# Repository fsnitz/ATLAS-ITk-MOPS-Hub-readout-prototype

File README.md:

# MPSoC-based MOPS-Hub readout board — supplementary project files

This repository accompanies the master's thesis **“Development of an MPSoC-based readout board as a verification method and interface for the ATLAS ITk MOPS-Hub communication interface”** (2024).

The work addresses an intermediate readout system for the ATLAS Inner Tracker (ITk) Pixel Detector Control System. It uses the AMD Kria K26 System-on-Module (SoM) with programmable logic (PL) and a processing system (PS), PetaLinux, an AXI-based shared-memory interface, and an electrical link (eLink) to communicate with the MOPS-Hub. The **eLink** is the electrical communication link; the **eLink Core** is its FPGA firmware implementation.

> **Project status:** The PL–PS shared-memory interface was successfully tested. The eLink interface exhibited firmware-timing and hardware/signal-integrity limitations. Full readout-chain functionality was **not verified** within the thesis. The published files should therefore be treated as research and development artifacts, not as a validated production design.
>
> **Before publishing this repository:** Copy the actual project files into the paths listed below, preserving capitalization and filenames. These links are derived from the original thesis appendix and cannot be verified until the repository has been populated. Check that you have permission to redistribute third-party documentation, vendor files, externally developed tools, and CERN/project-specific materials. If a file cannot be released, remove its repository link and cite the authorized upstream source instead.

## Getting started

1. Consult the thesis for the system architecture, implementation decisions, test setup, results, and limitations.
2. For Vivado project generation, start with the [firmware build instructions](Firmware/BuildScripts/README.md) and the relevant build script below. The thesis used the **2023.2** versions of Vivado and PetaLinux; confirm any additional requirements in the build instructions.
3. For embedded Linux, see the [PetaLinux projects](Software/PetaLinuxProjects/) and associated tools under [ToolsAndLibs](Software/ToolsAndLibs/).
4. For the eLink adapter, see the [KR260 eLink-hat revisions](Hardware/KR260eLinkHat/). The second revision includes changes for receiver-side common-mode biasing.
5. Use a tagged release of this repository when reproducing the thesis, because its main development branch may change over time.

## Repository contents

This [README](README.md) is the index of the supplementary materials.

The five principal directories are [Hardware/](Hardware/), [Firmware/](Firmware/), [Software/](Software/), [Documentation/](Documentation/), and [Miscellaneous/](Miscellaneous/). Links below are **relative to the root of this repository**.

### Hardware

- [Hardware/KR260eLinkHat/](Hardware/KR260eLinkHat/) — adapter board for interfacing the KR260 evaluation board with the eLink signals.
  - [rev01/](Hardware/KR260eLinkHat/rev01/) — initial design, used during the thesis.
    - [KR260eLinkHatSchematics_Rev01.pdf](Hardware/KR260eLinkHat/rev01/KR260eLinkHatSchematics_Rev01.pdf) — revision 01 schematic (thesis Appendix A.1).
    - [eLinkHatPCB_Rev01.pdf](Hardware/KR260eLinkHat/rev01/eLinkHatPCB_Rev01.pdf) — revision 01 PCB layout (Appendix A.2).
  - [rev02/](Hardware/KR260eLinkHat/rev02/) — revision incorporating biasing changes for LVDS receiver common-mode voltage.
    - [KR260eLinkHatSchematics_Rev02.pdf](Hardware/KR260eLinkHat/rev02/KR260eLinkHatSchematics_Rev02.pdf) — revision 02 schematic (Appendix A.3).
    - [eLinkHatPCB_Rev02.pdf](Hardware/KR260eLinkHat/rev02/eLinkHatPCB_Rev02.pdf) — revision 02 PCB layout (Appendix A.4).
- [Hardware/Library/](Hardware/Library/) — KiCad symbols, footprints, and 3D models supplementing the standard libraries.
- [Hardware/MOPS-Hub_Readout_board/](Hardware/MOPS-Hub_Readout_board/) — preliminary design files for a dedicated K26 SoM-based MOPS-Hub readout board.

### Firmware

- [Firmware/BuildScripts/](Firmware/BuildScripts/) — Vivado build scripts and setup guidance.
  - [MopsHubReadoutBoard_build.tcl](Firmware/BuildScripts/MopsHubReadoutBoard_build.tcl) — readout board firmware design (thesis Appendix B.4).
  - [PLtoPS_Test_build.tcl](Firmware/BuildScripts/PLtoPS_Test_build.tcl) — PL–PS shared-memory interface test design (Appendix B.6).
  - [eLinkTestSim_build.tcl](Firmware/BuildScripts/eLinkTestSim_build.tcl) — eLink interface simulation design.
  - [eLinkTest_build.tcl](Firmware/BuildScripts/eLinkTest_build.tcl) — eLink interface hardware test design (Appendix B.7).
  - [README.md](Firmware/BuildScripts/README.md) — Vivado version information and build instructions.
- [Firmware/SourceFiles/](Firmware/SourceFiles/) — sources used by the firmware designs.
  - [BlockDesigns/](Firmware/SourceFiles/BlockDesigns/) — Vivado block designs.
  - [Constraints/](Firmware/SourceFiles/Constraints/) — I/O and timing constraints.
  - [HDL/](Firmware/SourceFiles/HDL/) — VHDL and Verilog sources, including supporting components used by the eLink firmware implementation.
- [Firmware/ConfigurationFiles/](Firmware/ConfigurationFiles/) — PP3-FPGA module configuration files used during testing. Record the exact version used in each experiment.

### Software

- [Software/PetaLinuxProjects/](Software/PetaLinuxProjects/) — files for preparing the KR260 embedded Linux systems, including the necessary BSP and hardware design resources as described in the thesis.
  - [PLtoPS_Test/](Software/PetaLinuxProjects/PLtoPS_Test/) — shared-memory interface test (thesis Section 7.1).
  - [MopsHubReadoutBoard/](Software/PetaLinuxProjects/MopsHubReadoutBoard/) — readout board and proposed full-chain test project (thesis Section 7.3). The corresponding register map and hardware-access files are associated with this project.
  - [K26_StarterKit/](Software/PetaLinuxProjects/K26_StarterKit/) — starter BSP files from which the thesis projects were derived.
  - [epos-rootfs/](Software/PetaLinuxProjects/epos-rootfs/) — AlmaLinux 9-based root filesystem materials.
- [Software/ToolsAndLibs/](Software/ToolsAndLibs/) — supporting tools and libraries.
  - [xsa-to-overlays/](Software/ToolsAndLibs/xsa-to-overlays/) — Python tool for preparing Device Tree-related files from a hardware design.
  - [PuzzledLizardWizard/](Software/ToolsAndLibs/PuzzledLizardWizard/) — Python tool for generating a Hardware Access Library (HAL) from a register-map JSON file.
  - [libuio-bugFix/](Software/ToolsAndLibs/libuio-bugFix/) — library files for user-space I/O access under embedded Linux.

The original appendix additionally mentions a `HalFiles` subdirectory inside the PetaLinux projects, but does not establish its full relative path. Add a direct link here after confirming its location in the repository.

### Documentation

- [Documentation/](Documentation/) — source documents referred to during development. **Check redistribution rights before committing any documents listed here.**
  - [KR260_schematics.pdf](Documentation/KR260_schematics.pdf) — KR260 evaluation board schematics.
  - [DS987_K26_Datasheet.pdf](Documentation/DS987_K26_Datasheet.pdf) — K26 SoM data sheet.
  - [Kria_K26_SOM_PinMapping.pdf](Documentation/Kria_K26_SOM_PinMapping.pdf) — K26 SoM connector and MPSoC pin mapping.
  - [OpcSpringer.pdf](Documentation/OpcSpringer.pdf) — book on OPC and OPC UA; **do not redistribute unless permission/licensing explicitly allows it**. Prefer a publisher or DOI link.
  - [EMP_Setup_guide.pdf](Documentation/EMP_Setup_guide.pdf) — EMP-group setup guide; **confirm that public distribution is authorized**.

### Miscellaneous

- [Miscellaneous/BlockDesignPrints/](Miscellaneous/BlockDesignPrints/) — PDF exports of firmware block diagrams reproduced in the thesis.
  - [InitialBD.pdf](Miscellaneous/BlockDesignPrints/InitialBD.pdf) — initial readout-board design (Appendix B.1).
  - [InitialBDstripped.pdf](Miscellaneous/BlockDesignPrints/InitialBDstripped.pdf) — simplified initial firmware (Appendix B.2).
  - [ExampleProject.pdf](Miscellaneous/BlockDesignPrints/ExampleProject.pdf) — register-map example (Appendix B.3).
  - [SystemOverview.pdf](Miscellaneous/BlockDesignPrints/SystemOverview.pdf) — readout board system overview (Appendix B.4).
  - [eLinkBD.pdf](Miscellaneous/BlockDesignPrints/eLinkBD.pdf) — readout-board eLink block (Appendix B.5).
  - [PLtoPS_BD.pdf](Miscellaneous/BlockDesignPrints/PLtoPS_BD.pdf) — PL–PS interface test (Appendix B.6).
  - [eLinkTestBD.pdf](Miscellaneous/BlockDesignPrints/eLinkTestBD.pdf) — eLink test project (Appendix B.7).
  - [eLinkTesteLinkBlockDB.pdf](Miscellaneous/BlockDesignPrints/eLinkTesteLinkBlockDB.pdf) — additional block diagram used in the eLink interface test.
- [Miscellaneous/CodeSnippets/](Miscellaneous/CodeSnippets/) — sources for code snippets reproduced in the thesis.
  - [PLtoPS_Test_regs.json](Miscellaneous/CodeSnippets/PLtoPS_Test_regs.json) — airhdl register map for the PL–PS interface test (Appendix C.1).
- [Miscellaneous/DrawIoSource/](Miscellaneous/DrawIoSource/) — editable diagrams drawn for the thesis.
- [Miscellaneous/Figures/](Miscellaneous/Figures/) — figures used in the thesis.

## Reproducibility and release information

Record the version/tag used for each public thesis release, along with relevant dependencies, hardware revisions, and tool versions. If possible, identify the exact PP3-FPGA firmware configuration used for each test. When a stable release is available, archive it in a long-term research repository and cite the corresponding persistent identifier in the published thesis.

The root directory and file names above follow the *original digital appendix*. Only the thesis appendix was supplied for this README; the supplementary hardware, firmware, software, and documentation files themselves have **not** been inspected or validated in this draft.

## Citation

**Thesis:** Felix Sebastian Nitz, *Development of an MPSoC-based readout board as a verification method and interface for the ATLAS ITk MOPS-Hub communication interface*, Master's thesis, Cologne University of Applied Sciences, 2024.

**Repository:** Cite the released repository version and its eventual DOI or version-specific URL when available. Add a `CITATION.cff` file once the repository metadata and release details are finalized.

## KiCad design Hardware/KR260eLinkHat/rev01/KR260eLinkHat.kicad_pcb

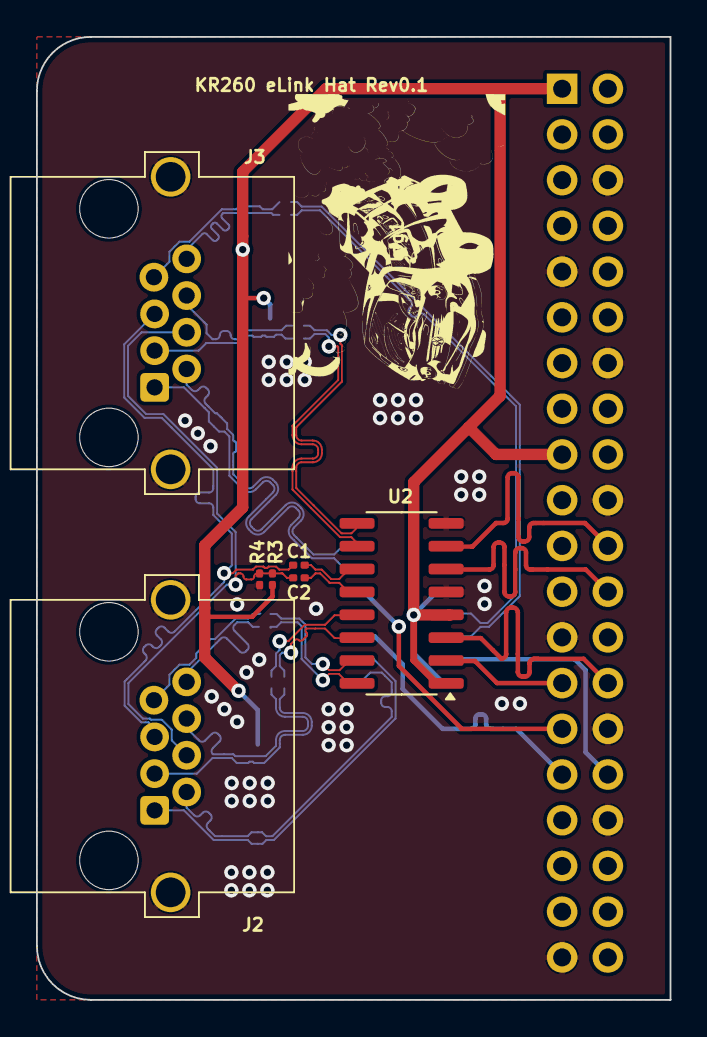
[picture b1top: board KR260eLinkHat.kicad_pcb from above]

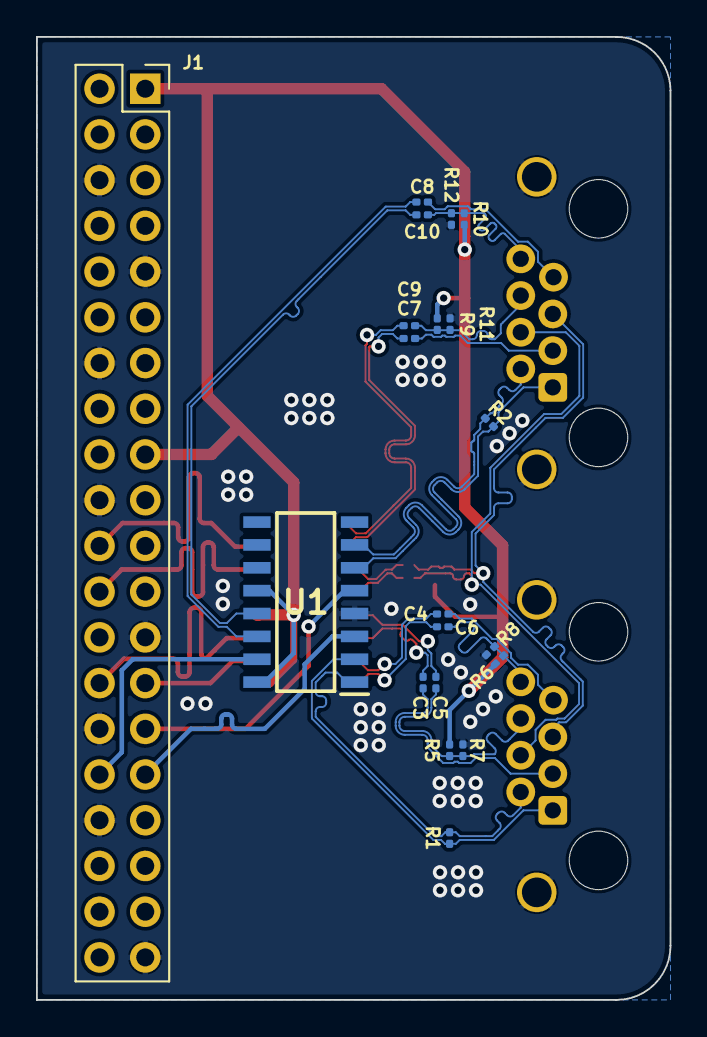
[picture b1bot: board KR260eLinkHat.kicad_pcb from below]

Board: 4 copper layers, 35.2 x 53.5 mm, 28 parts (20 on the bottom side), 33 nets.

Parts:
C1, C2, C3, C4, C5, C6, C7, C8, C9, C10: 10nF; C_0201_0603Metric
J1: PinSocket_2x20_P2.54mm; RpiHat
J2, J3: RJ45_Shielded; WR-MJ Modular Jack Horizontal Shielded_615008140621
R1, R2: 100R; R_0201_0603Metric
R3, R5, R6, R9, R10: 10K; R_0201_0603Metric
R4, R7, R8, R11, R12: 47K; R_0201_0603Metric
U1: SN65LVDS050DR; SOIC127P600X175-16N
U2: SN65LVDS047DR; SOIC-16_3.9x9.9mm_P1.27mm
log1: BulliLogo

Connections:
+3V3: J1.1 (3V3), J1.17 (3V3), R3.2, R5.2, R6.2, R9.2, R10.2, U1.12 (DE), U1.16 (VCC), U2.1 (EN), U2.4 (VCC)
/0V6_CLK_N: C2.2, J2.4, J3.4, R3.1, R4.2
/0V6_CLK_P: C1.2, J2.5, J3.5
/0V6_RX0_N: J2.2, R1.1, U1.1 (1B)
/0V6_RX0_P: J2.1, R1.2, U1.2 (1A)
/0V6_RX1_N: J3.2, R2.1, U1.7 (2B)
/0V6_RX1_P: J3.1, R2.2, U1.6 (2A)
/0V6_Reset0_N: C6.2, J2.8, R6.1, R8.2
/0V6_Reset0_P: C4.2, J2.7
/0V6_Reset1_N: C10.2, J3.8, R10.1, R12.2
/0V6_Reset1_P: C8.2, J3.7
/0V6_TX0_N: C5.2, J2.6, R5.1, R7.2
/0V6_TX0_P: C3.2, J2.3
/0V6_TX1_N: C9.2, J3.6, R9.1, R11.2
/0V6_TX1_P: C7.2, J3.3
/CLK: J1.24 (~CE0/GPIO8), U2.6 (DIN3)
/CLK_N: C2.1, U2.12 (DOUT3-)
/CLK_P: C1.1, U2.11 (DOUT3+)
/RX0: J1.31 (GCLK2/GPIO6), U1.3 (1R)
/RX1: J1.29 (GCLK1/GPIO5), U1.5 (2R)
/Reset0: J1.27 (ID_SD/GPIO0), U2.2 (DIN1)
/Reset0_N: C6.1, U2.16 (DOUT1-)
/Reset0_P: C4.1, U2.15 (DOUT1+)
/Reset1: J1.32 (PWM0/GPIO12), U1.15 (1D)
/Reset1_N: C10.1, U1.13 (1Z)
/Reset1_P: C8.1, U1.14 (1Y)
/TX0: J1.28 (ID_SC/GPIO1), U2.3 (DIN2)
/TX0_N: C5.1, U2.13 (DOUT2-)
/TX0_P: C3.1, U2.14 (DOUT2+)
/TX1: J1.22 (GPIO25), U2.7 (DIN4)
/TX1_N: C9.1, U2.9 (DOUT4-)
/TX1_P: C7.1, U2.10 (DOUT4+)
GND: J1.6 (GND), J1.9 (GND), J1.14 (GND), J1.20 (GND), J1.25 (GND), J1.30 (GND), J1.34 (GND), J1.39 (GND), J2.SH, J3.SH, R4.1, R7.1, R8.1, R11.1, R12.1, U1.4 (~RE), U2.5 (GND), U2.8 (~EN)

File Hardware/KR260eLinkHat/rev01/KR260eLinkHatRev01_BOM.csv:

"Reference","Value","Description","Datasheet","Footprint","Mouser Part Number","Qty"
"C1,C2,C3,C4,C5,C6,C7,C8,C9,C10","10nF","Unpolarized capacitor","https://www.mouser.de/datasheet/2/447/UPY_NP0X5R_01005_4V_to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","Capacitor_SMD:C_0201_0603Metric","603-CC0201JX7R6BB103","10"
"J1","PinSocket_2x20_P2.54mm","Vorhanden im Labor (Schrank 1) ","","Connector_PinSocket_2.54mm:PinSocket_2x20_P2.54mm_Vertical","","1"
"J2,J3","RJ45_Shielded","9x vorhanden in der PP3-FPGA Teilekiste ","https://www.we-online.com/components/products/datasheet/6150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","ReadoutBoard_Footprints:WR-MJ Modular Jack Horizontal Shielded_615008140621","710-615008140621","2"
"R1,R2","100R","Resistor","https://www.mouser.de/datasheet/2/315/AOA0000C304-1149620.pdf","Resistor_SMD:R_0201_0603Metric","667-ERJ-1RKD1000C","2"
"R3,R5,R6,R9,R10","10K","Resistor","https://www.mouser.de/datasheet/2/447/PYu_RE_105_RoHS_L_6-30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","Resistor_SMD:R_0201_0603Metric","603-RE0201BRE0710KL","5"
"R4,R7,R8,R11,R12","47K","Resistor","https://www.mouser.de/datasheet/2/447/PYu_RE_105_RoHS_L_6-30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","Resistor_SMD:R_0201_0603Metric","603-RE0201BRE0747KL","5"
"U2","SN65LVDS047DR","Quad LVDS Differential Line Driver, 400Mbps, SOIC-16","http://www.ti.com/lit/ds/symlink/sn65lvds047.pdf","Package_SO:SOIC-16_3.9x9.9mm_P1.27mm","595-SN65LVDS047DR","1"
"U1","SN65LVDS050DR","Dual LVDS Transmitter/Receiver","http://www.ti.com/lit/gpn/sn65lvds050","SOIC127P600X175-16N","595-SN65LVDS050DR","1"
